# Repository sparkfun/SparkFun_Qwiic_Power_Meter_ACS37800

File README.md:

-----------------------------

The SparkFun Qwiic Power Meter - ACS37800 lets you measure voltage up to 60VDC and current up to &plusmn;30A over I<sup>2</sup>C. This board features the ACS37800 power monitor IC from Allegro Microsystems which uses a hall-effect, galvanically isolated current sensing technology to achieve reinforced isolation ratings on a small board footprint. This breakout integrates the ACS37800 into the Qwiic ecosystem to easily communicate over I<sup>2</sup>C. 

Although the ACS37800 power monitoring IC is capable of monitoring AC power at high line voltages, the SparkFun Qwiic Power Meter is designed for Safety Extra Low Voltage (SELV) applications of up to 60VDC only. Its use in AC power systems is not recommended.

Repository Contents
-------------------

* **/docs** - Hookup Guide files
* **/Hardware** - Eagle design files (.brd, .sch)
* **/Production** - Production panel files (.brd)

Documentation
--------------
* **[Library](https://github.com/sparkfun/SparkFun_ACS37800_Power_Monitor_Arduino_Library)** - Arduino library for the SparkFun Qwiic Power Meter - ACS37800.
* **[Hookup Guide](https://docs.sparkfun.com/SparkFun_Qwiic_Power_Meter_ACS37800)** - Basic hookup guide for the SparkFun Qwiic Power Meter - ACS37800.

Product Versions
----------------
* [SPX-17873](https://www.sparkfun.com/sparkx-power-meter-acs37800-qwiic.html) - Initial SparkX Release
* [SEN-29259](https://www.sparkfun.com/sparkfun-power-meter-acs37800-qwiic.html) - Initial SparkFun Release

License Information
-------------------

This product is _**open source**_! 

Please review the LICENSE.md file for license information. 

If you have any questions or concerns on licensing, please contact technical support on our [SparkFun forums](https://forum.sparkfun.com/viewforum.php?f=152).

Distributed as-is; no warranty is given.

- Your friends at SparkFun.

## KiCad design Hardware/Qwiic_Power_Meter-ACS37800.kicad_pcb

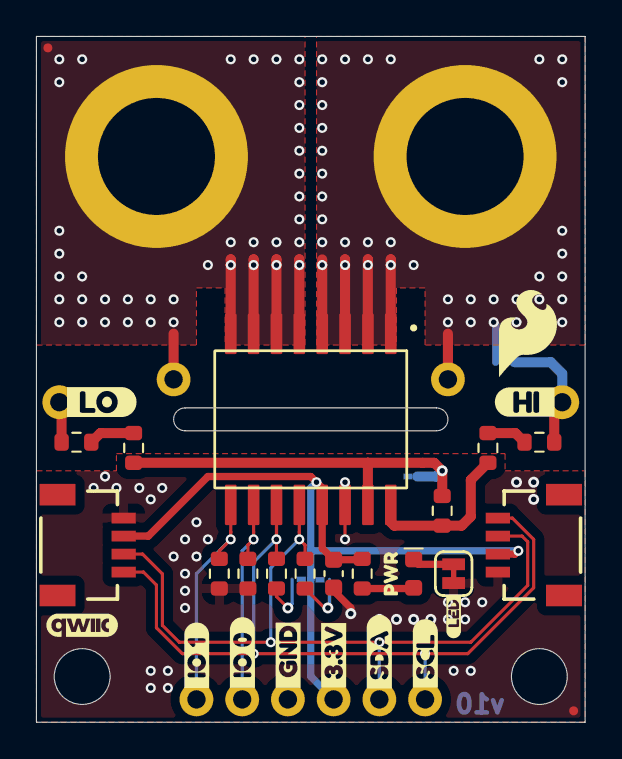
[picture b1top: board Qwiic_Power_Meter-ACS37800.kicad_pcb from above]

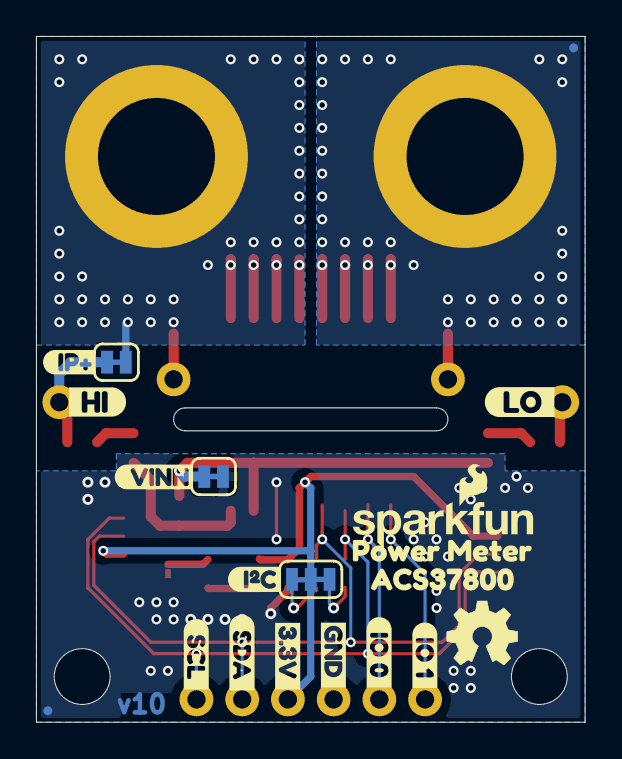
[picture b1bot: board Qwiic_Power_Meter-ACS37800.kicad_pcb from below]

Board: 2 copper layers, 30.5 x 38.1 mm, 59 parts (19 on the bottom side), 18 nets.

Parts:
C1: 0.1uF; C_0603_1608Metric
D1: Red; LED_0603_1608Metric_Red
FID1, FID2, FID3, FID4: Fiducial_0.5mm; Fiducial_0.5mm_Mask1mm
G1: OSHW_Logo; Creative_Commons_License
IP+1: Jumper_2_NC_Trace
J1, J4, J5, J6, J10, J11: Conn_01x01; 1x01
J3, J7: Qwiic_RA; JST_SMD_1.0mm-4_Black
J8, J9: Conn_01x01; 1x01_0.4in
J12: I2C; 1x04
JP1: LED; Jumper_2_NC_Trace
JP2: I2C; Jumper_3_NC-2_Trace
R2, R9, R10, R11: 1M; R_0603_1608Metric
R3: 8.2k; R_0603_1608Metric
R4: 1k; R_0603_1608Metric
R5, R6, R7, R8: 4.7k; R_0603_1608Metric
Ref**: Val**; OSHW_Logo_4mm
ST1, ST2: Standoff
U1: ACS37800; SO-16_Wide_Power
VINN1: Jumper_2_NC_Trace
kibuzzard-67B80BA2: G***; kibuzzard-67B80BA2
kibuzzard-68C98CE2: G***; kibuzzard-68C98CE2
kibuzzard-68C98CF7: G***; kibuzzard-68C98CF7
kibuzzard-68C98D0A: G***; kibuzzard-68C98D0A
kibuzzard-68C98D92: G***; kibuzzard-68C98D92
kibuzzard-68C98DAC: G***; kibuzzard-68C98DAC
kibuzzard-68C98DC2: G***; kibuzzard-68C98DC2
kibuzzard-68C98DD6: G***; kibuzzard-68C98DD6
kibuzzard-68C98DF7: G***; kibuzzard-68C98DF7
kibuzzard-68C98E17: G***; kibuzzard-68C98E17
kibuzzard-68C98F03: G***; kibuzzard-68C98F03
kibuzzard-68C98FF6: G***; kibuzzard-68C98FF6
kibuzzard-68C9901D: G***; kibuzzard-68C9901D
kibuzzard-68C9907C: G***; kibuzzard-68C9907C
kibuzzard-68C9913E: G***; kibuzzard-68C9913E
kibuzzard-68C9961E: G***; kibuzzard-68C9961E
kibuzzard-68C99001: G***; kibuzzard-68C99001
kibuzzard-68C99018: G***; kibuzzard-68C99018
kibuzzard-68C99023: G***; kibuzzard-68C99023
kibuzzard-68C99027: G***; kibuzzard-68C99027
kibuzzard-68C99085: G***; kibuzzard-68C99085
kibuzzard-68C99129: G***; kibuzzard-68C99129
kibuzzard-68C99652: G***; kibuzzard-68C99652

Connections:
3.3V: C1.1, J3.2, J7.2, J12.2, JP2.2 (B), R4.1, U1.13 (VCC)
GND: C1.2, J3.1, J7.1, J12.1, JP1.1 (A), R5.1, R6.1, U1.14 (GND), VINN1.2 (B)
IO0: J6.1, R5.2, U1.10 (DIO_0)
IO1: J1.1, R6.2, U1.9 (DIO_1)
IP+: IP+1.2 (B), J8.1, J11.1, U1.1 (IP+), U1.2 (IP+), U1.3 (IP+), U1.4 (IP+)
IP-: J9.1, J10.1, U1.5 (IP-), U1.6 (IP-), U1.7 (IP-), U1.8 (IP-)
unnamed: D1.2 (A), R4.2
unnamed: D1.1 (K), JP1.2 (B)
unnamed: IP+1.1 (A), J4.1, R2.1
unnamed: J5.1, R10.1
unnamed: JP2.1 (A), R8.2
unnamed: JP2.3 (C), R7.2
unnamed: R2.2, R9.1
unnamed: R10.2, R11.1
SCL: J3.4, J7.4, J12.4, R8.1, U1.11 (SCL)
SDA: J3.3, J7.3, J12.3, R7.1, U1.12 (SDA)
VINN: R3.1, R11.2, U1.15 (VINN), VINN1.1 (A)
VINP: R3.2, R9.2, U1.16 (VINP)

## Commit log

2025-02-21 v10 ready for review
2025-02-22 Add missing fiducials
2025-02-24 Update SOIC Wide footprint
2025-02-24 Update 0.4in symbol and FP
2025-04-30 Saved in KiCad 9
2025-04-30 Adds measures, labels LED jumper, updates some schematic text
2025-04-30 Add missed measure
2025-04-30 Makes design 2-layer, updates jumper names in schematic
2025-06-25 Fixes some missing traces
2025-07-11 Adds ordering instructions, updates design by, revised by
2025-07-11 Adds some more notes to the design
2025-09-16 Fixes silk
2025-09-16 Adds fiducials and standoffs, changes the silk on the underside
2025-09-16 Adds some measures
2026-01-20 Updates 1x01 labels in the schematic, fixes some jumper labels
2026-01-22 Documentation commit
    Adding Hookup Guide content after initial review.
2026-01-22 Docs update
    Updating board files and adding GH pages build file.
2026-06-03 Deployed 083435b with MkDocs version: 1.6.1
2026-06-10 Update baud rate in quickstart instructions

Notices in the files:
parts and their libraries:
Released under the Creative Commons Attribution Share-Alike 4.0 License
https://creativecommons.org/licenses/by-sa/4.0
